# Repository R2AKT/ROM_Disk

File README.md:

License addendum - https://github.com/R2AKT/ROM_Disk/blob/main/Addendum.txt
# ROM_Disk

ROM disk board. For Mega-80 (Mega-580) DIY 8-bit micro-computer - https://github.com/R2AKT/Mega-80.

Based on ROM-disk for RADIO-86RK.

Плата ROM-диска. Для самодельной 8-битной микро-ЭВМ - https://github.com/R2AKT/Mega-80.

На основе ROM-диска для РАДИО-86РК.

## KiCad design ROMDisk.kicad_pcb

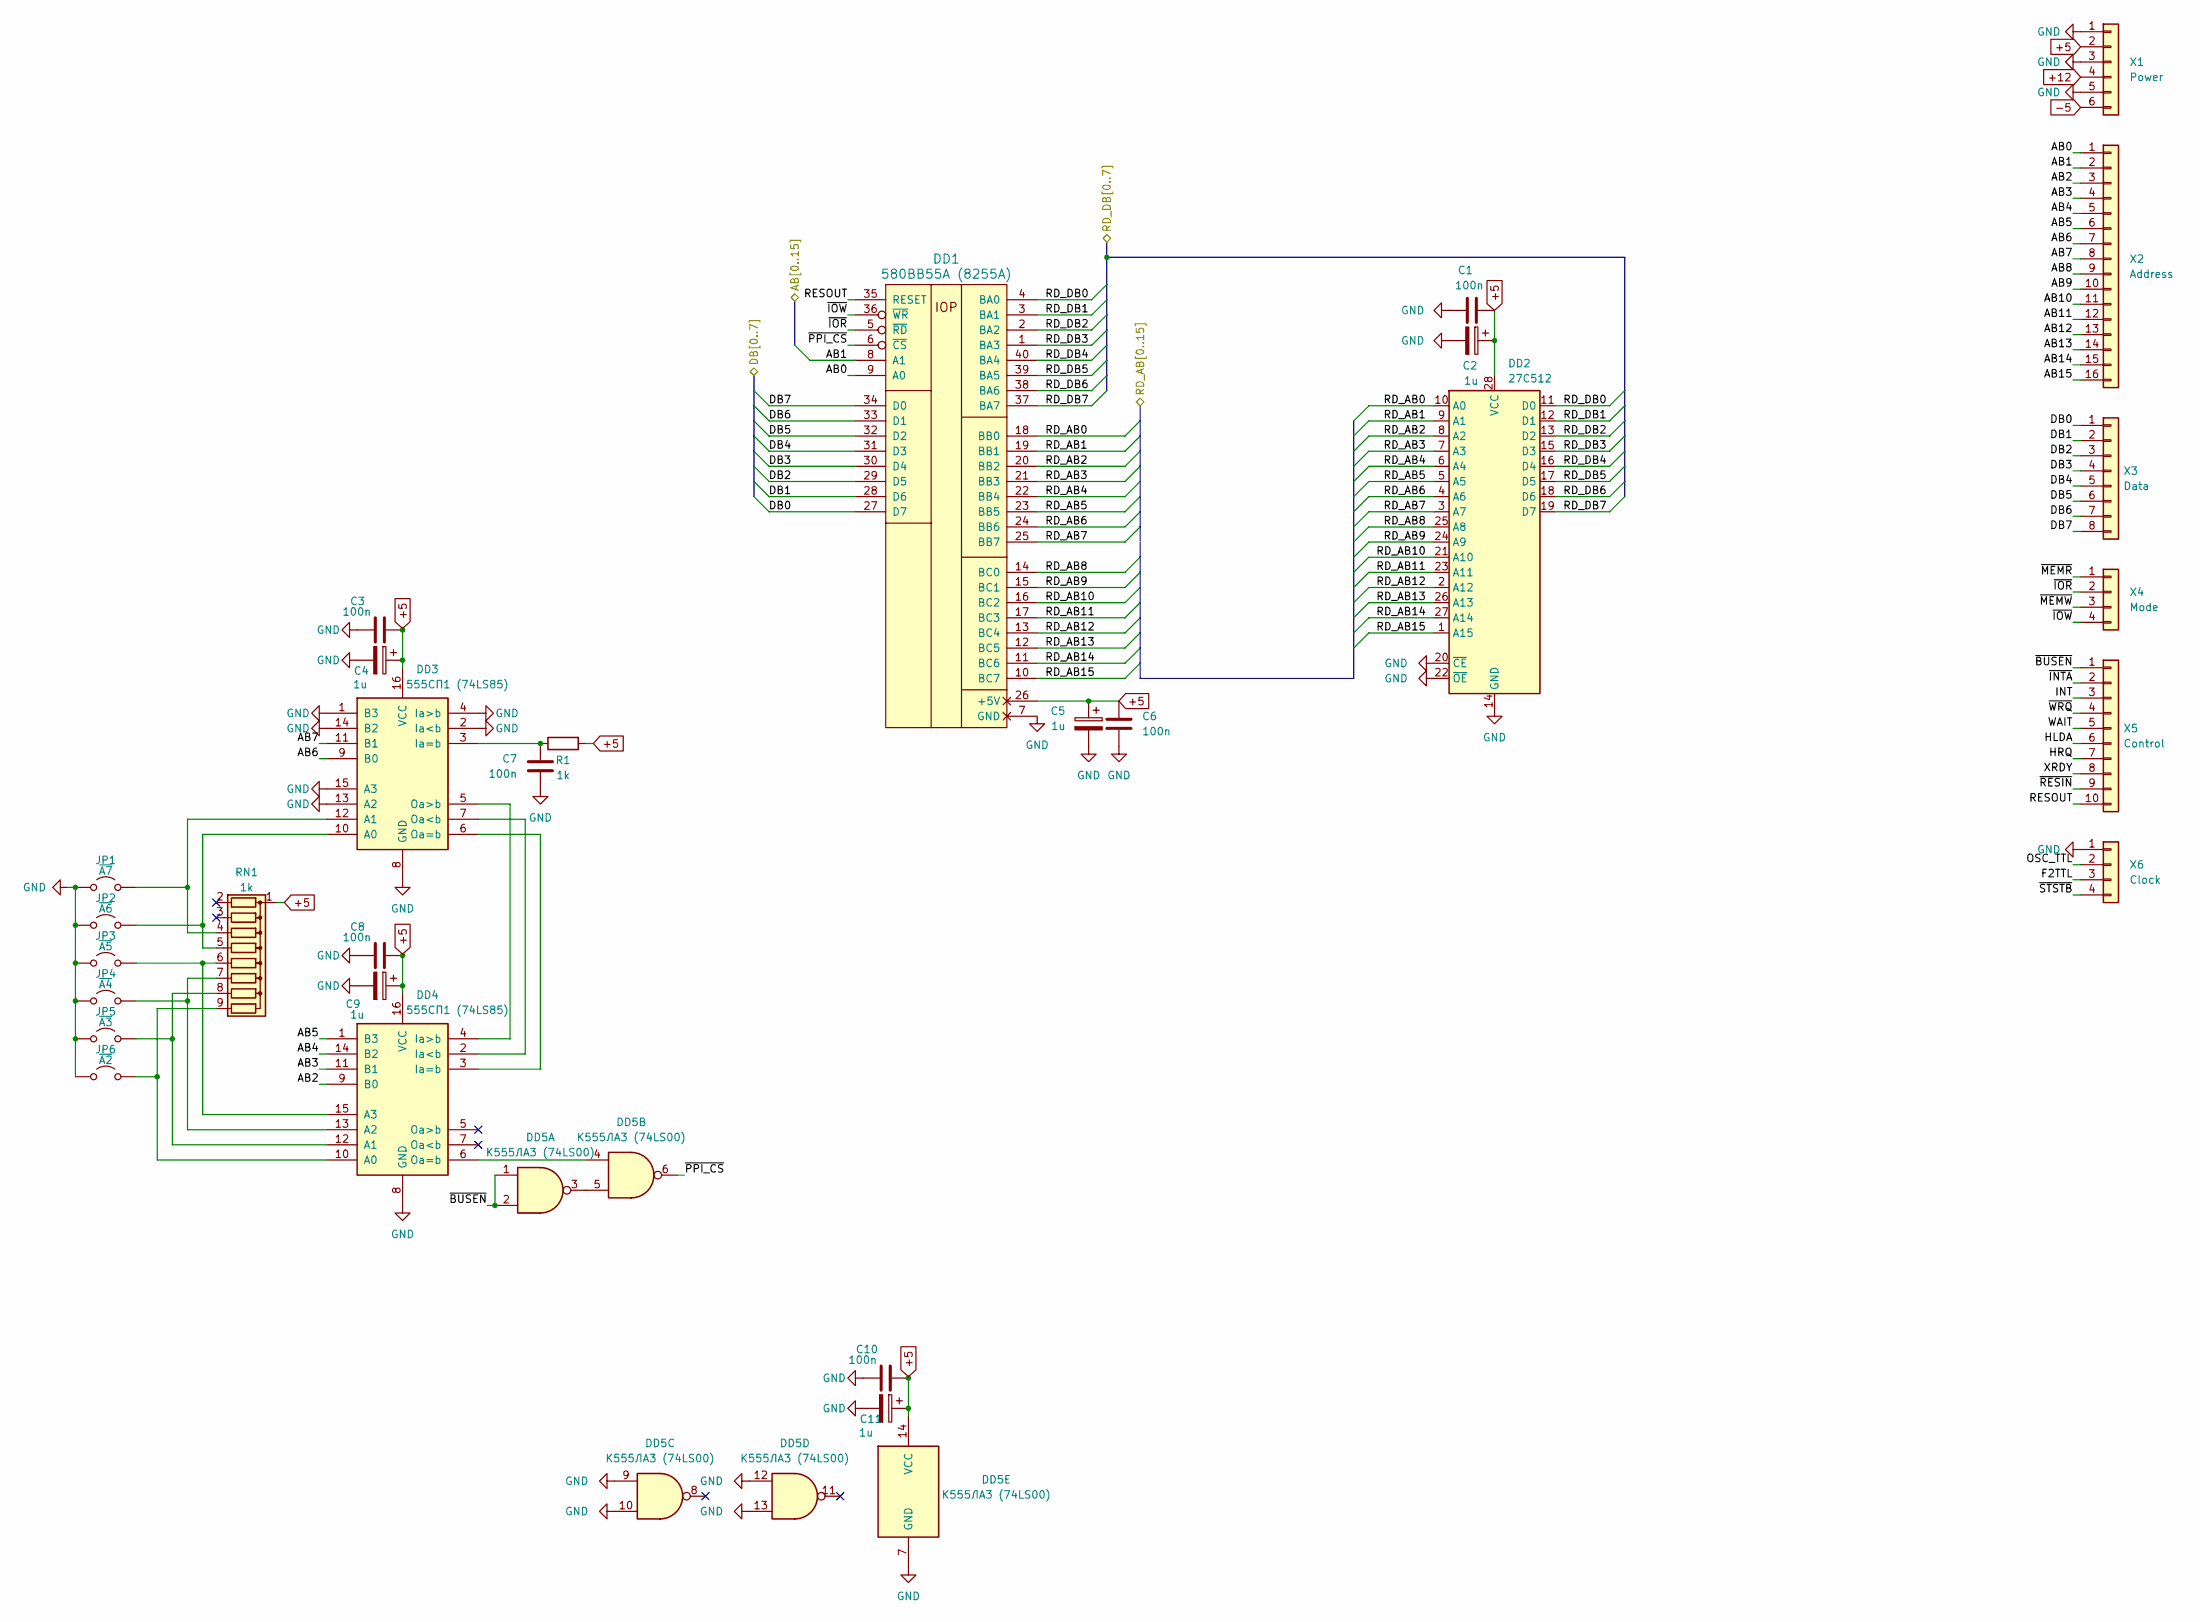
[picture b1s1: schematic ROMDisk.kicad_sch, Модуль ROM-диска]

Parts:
C1, C3, C6, C7, C8, C10: 100n; C_0805_2012Metric_Pad1.18x1.45mm_HandSolder
C2, C4, C5, C9, C11: 1u; CP_EIA-3216-18_Kemet-A_Pad1.58x1.35mm_HandSolder
DD1: 580ВВ55A (8255A); DIP-40_W15.24mm_Socket_LongPads
DD2: 27C512; DIP-28_W15.24mm_Socket_LongPads
DD3, DD4: 555СП1 (74LS85); DIP-16_W7.62mm_Socket_LongPads
DD5: К555ЛА3 (74LS00); DIP-14_W7.62mm_Socket_LongPads
JP1: ~{A7}; SolderJumper-2_P1.3mm_Open_RoundedPad1.0x1.5mm
JP2: ~{A6}; SolderJumper-2_P1.3mm_Open_RoundedPad1.0x1.5mm
JP3: ~{A5}; SolderJumper-2_P1.3mm_Open_RoundedPad1.0x1.5mm
JP4: ~{A4}; SolderJumper-2_P1.3mm_Open_RoundedPad1.0x1.5mm
JP5: ~{A3}; SolderJumper-2_P1.3mm_Open_RoundedPad1.0x1.5mm
JP6: ~{A2}; SolderJumper-2_P1.3mm_Open_RoundedPad1.0x1.5mm
R1: 1k; R_0805_2012Metric_Pad1.20x1.40mm_HandSolder
RN1: 1k; R_Array_SIP9
X1: Power; PinHeader_1x06_P2.54mm_Vertical
X2: Address; PinHeader_1x16_P2.54mm_Vertical
X3: Data; PinHeader_1x08_P2.54mm_Vertical
X4: Mode; PinHeader_1x04_P2.54mm_Vertical
X5: Control; PinHeader_1x10_P2.54mm_Vertical
X6: Clock; PinHeader_1x04_P2.54mm_Vertical

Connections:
+5: C1.1, C2.1, C3.1, C4.1, C5.1, C6.1, C8.1, C9.1, C10.1, C11.1, DD1.26 (+5V), DD2.28 (VCC), DD3.16 (VCC), DD4.16 (VCC), DD5.14 (VCC), R1.2, RN1.1 (common), X1.2
+12: X1.4
-5: X1.6
/AB0: DD1.9 (A0), X2.1
/AB1: DD1.8 (A1), X2.2
/AB2: DD4.9 (B0), X2.3
/AB3: DD4.11 (B1), X2.4
/AB4: DD4.14 (B2), X2.5
/AB5: DD4.1 (B3), X2.6
/AB6: DD3.9 (B0), X2.7
/AB7: DD3.11 (B1), X2.8
/AB8: X2.9
/AB9: X2.10
/AB10: X2.11
/AB11: X2.12
/AB12: X2.13
/AB13: X2.14
/AB14: X2.15
/AB15: X2.16
/DB0: DD1.27 (D7), X3.1
/DB1: DD1.28 (D6), X3.2
/DB2: DD1.29 (D5), X3.3
/DB3: DD1.30 (D4), X3.4
/DB4: DD1.31 (D3), X3.5
/DB5: DD1.32 (D2), X3.6
/DB6: DD1.33 (D1), X3.7
/DB7: DD1.34 (D0), X3.8
/F2TTL: X6.3
/HLDA: X5.6
/HRQ: X5.7
/INT: X5.3
/OSC_TTL: X6.2
/RD_AB0: DD1.18 (BB0), DD2.10 (A0)
/RD_AB1: DD1.19 (BB1), DD2.9 (A1)
/RD_AB2: DD1.20 (BB2), DD2.8 (A2)
/RD_AB3: DD1.21 (BB3), DD2.7 (A3)
/RD_AB4: DD1.22 (BB4), DD2.6 (A4)
/RD_AB5: DD1.23 (BB5), DD2.5 (A5)
/RD_AB6: DD1.24 (BB6), DD2.4 (A6)
/RD_AB7: DD1.25 (BB7), DD2.3 (A7)
/RD_AB8: DD1.14 (BC0), DD2.25 (A8)
/RD_AB9: DD1.15 (BC1), DD2.24 (A9)
/RD_AB10: DD1.16 (BC2), DD2.21 (A10)
/RD_AB11: DD1.17 (BC3), DD2.23 (A11)
/RD_AB12: DD1.13 (BC4), DD2.2 (A12)
/RD_AB13: DD1.12 (BC5), DD2.26 (A13)
/RD_AB14: DD1.11 (BC6), DD2.27 (A14)
/RD_AB15: DD1.10 (BC7), DD2.1 (A15)
/RD_DB0: DD1.4 (BA0), DD2.11 (D0)
/RD_DB1: DD1.3 (BA1), DD2.12 (D1)
/RD_DB2: DD1.2 (BA2), DD2.13 (D2)
/RD_DB3: DD1.1 (BA3), DD2.15 (D3)
/RD_DB4: DD1.40 (BA4), DD2.16 (D4)
/RD_DB5: DD1.39 (BA5), DD2.17 (D5)
/RD_DB6: DD1.38 (BA6), DD2.18 (D6)
/RD_DB7: DD1.37 (BA7), DD2.19 (D7)
/RESOUT: DD1.35 (RESET), X5.10
/WAIT: X5.5
/XRDY: X5.8
/~BUSEN: DD5.1, DD5.2, X5.1
/~INTA: X5.2
/~IOR: DD1.5 (~RD), X4.2
/~IOW: DD1.36 (~WR), X4.4
/~MEMR: X4.1
/~MEMW: X4.3
/~PPI_CS: DD1.6 (~CS), DD5.6
/~RESIN: X5.9
/~STSTB: X6.4
/~WRQ: X5.4
GND: C1.2, C2.2, C3.2, C4.2, C5.2, C6.2, C7.2, C8.2, C9.2, C10.2, C11.2, DD1.7 (GND), DD2.14 (GND), DD2.20 (~CE), DD2.22 (~OE), DD3.1 (B3), DD3.2 (Ia<b), DD3.4 (Ia>b), DD3.8 (GND), DD3.13 (A2), DD3.14 (B2), DD3.15 (A3), DD4.8 (GND), DD5.7 (GND), DD5.9, DD5.10, DD5.12, DD5.13, JP1.1 (A), JP2.1 (A), JP3.1 (A), JP4.1 (A), JP5.1 (A), JP6.1 (A), X1.1, X1.3, X1.5, X6.1
unnamed: DD3.10 (A0), JP2.2 (B), RN1.5 (R4)
unnamed: DD3.12 (A1), JP1.2 (B), RN1.4 (R3)
unnamed: C7.1, DD3.3 (Ia=b), R1.1
unnamed: DD3.7 (Oa<b), DD4.2 (Ia<b)
unnamed: DD3.6 (Oa=b), DD4.3 (Ia=b)
unnamed: DD3.5 (Oa>b), DD4.4 (Ia>b)
unnamed: DD4.10 (A0), JP6.2 (B), RN1.9 (R8)
unnamed: DD4.12 (A1), JP5.2 (B), RN1.8 (R7)
unnamed: DD4.13 (A2), JP4.2 (B), RN1.7 (R6)
unnamed: DD4.15 (A3), JP3.2 (B), RN1.6 (R5)
unnamed: DD4.6 (Oa=b), DD5.4
unnamed: DD5.3, DD5.5

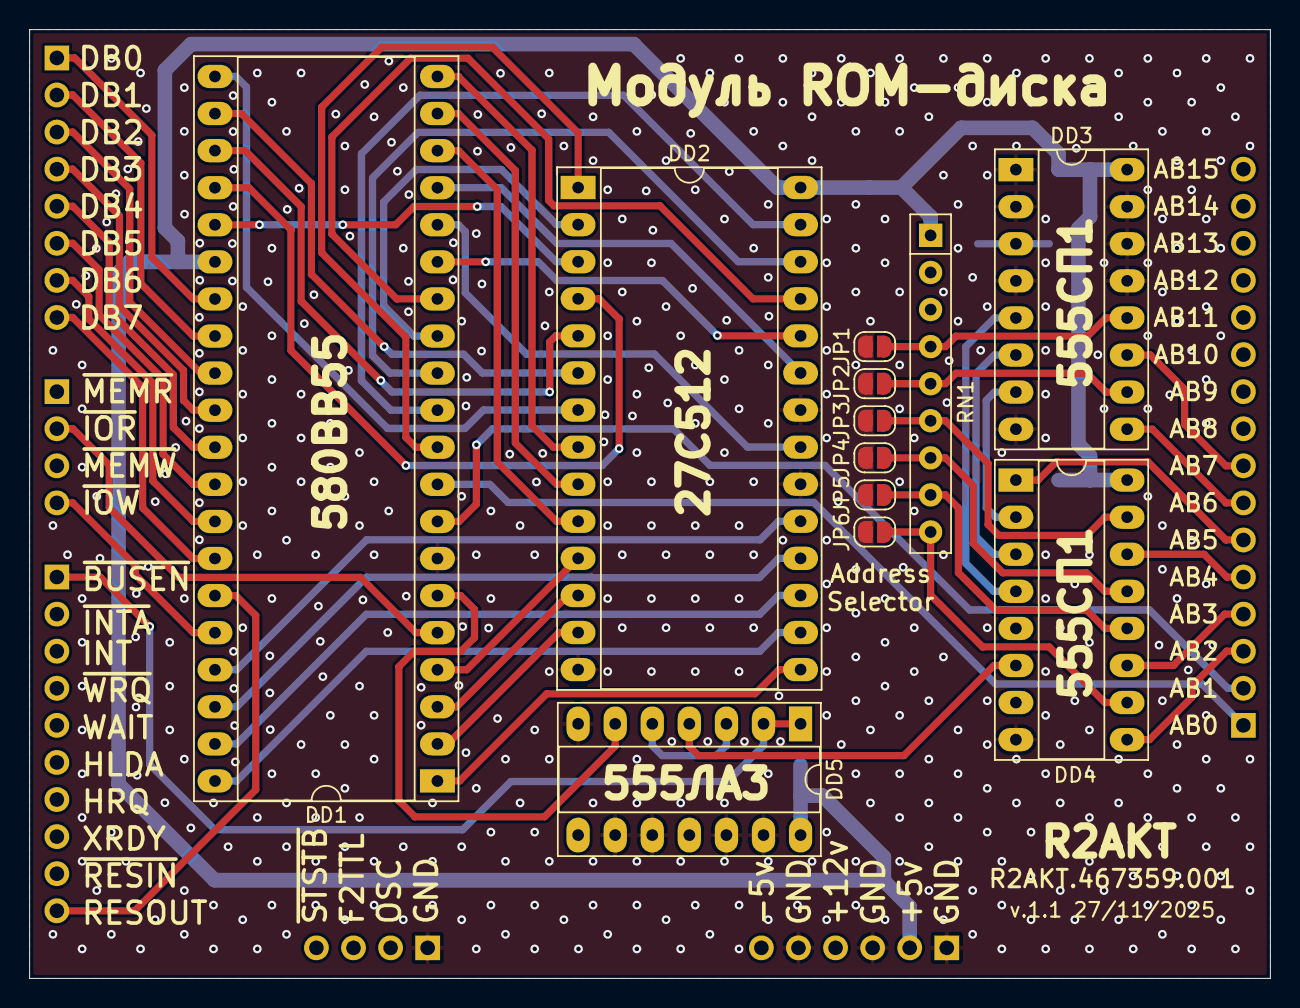
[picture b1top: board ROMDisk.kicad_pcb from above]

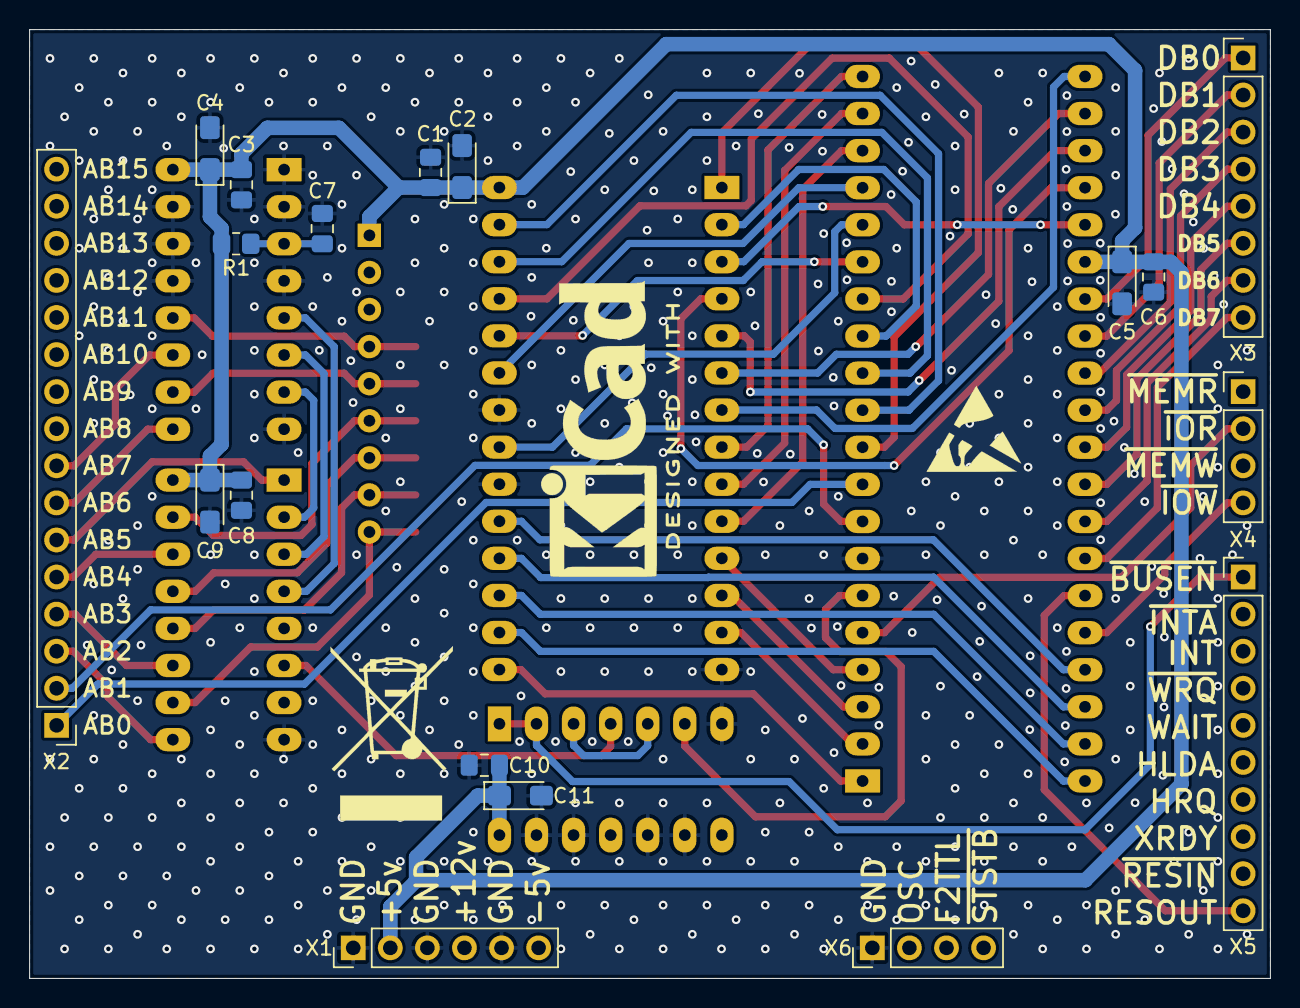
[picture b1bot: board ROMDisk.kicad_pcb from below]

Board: 2 copper layers, 85.0 x 65.0 mm, 30 parts (18 on the bottom side), 59 nets.

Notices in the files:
README.md:
License: MIT
